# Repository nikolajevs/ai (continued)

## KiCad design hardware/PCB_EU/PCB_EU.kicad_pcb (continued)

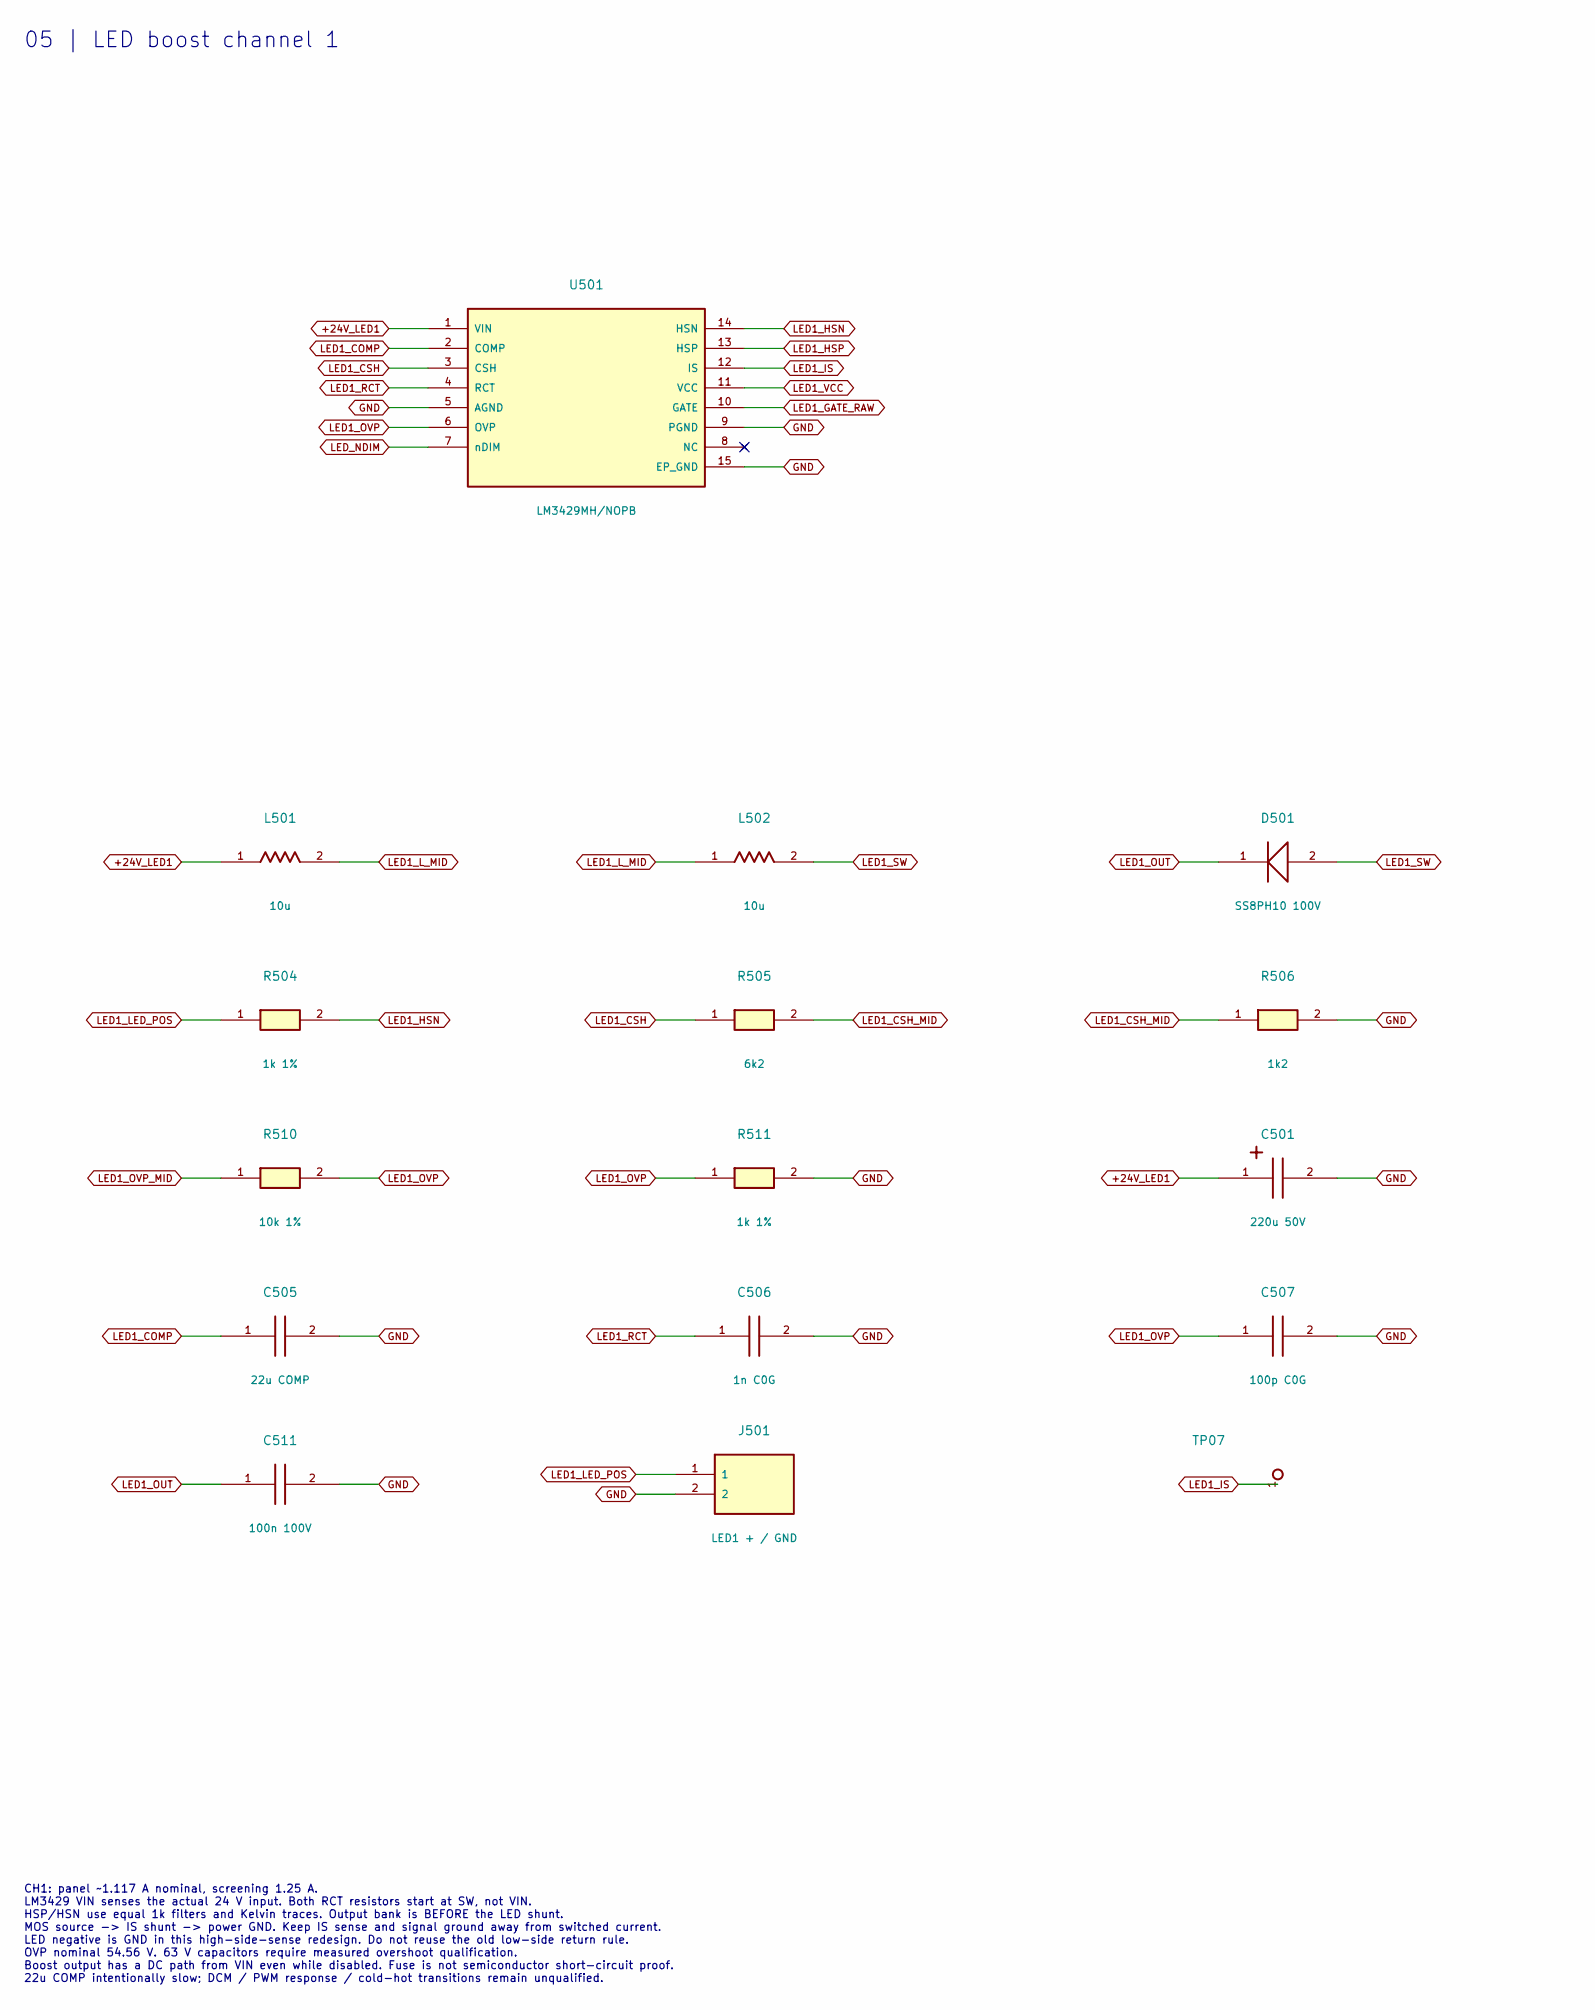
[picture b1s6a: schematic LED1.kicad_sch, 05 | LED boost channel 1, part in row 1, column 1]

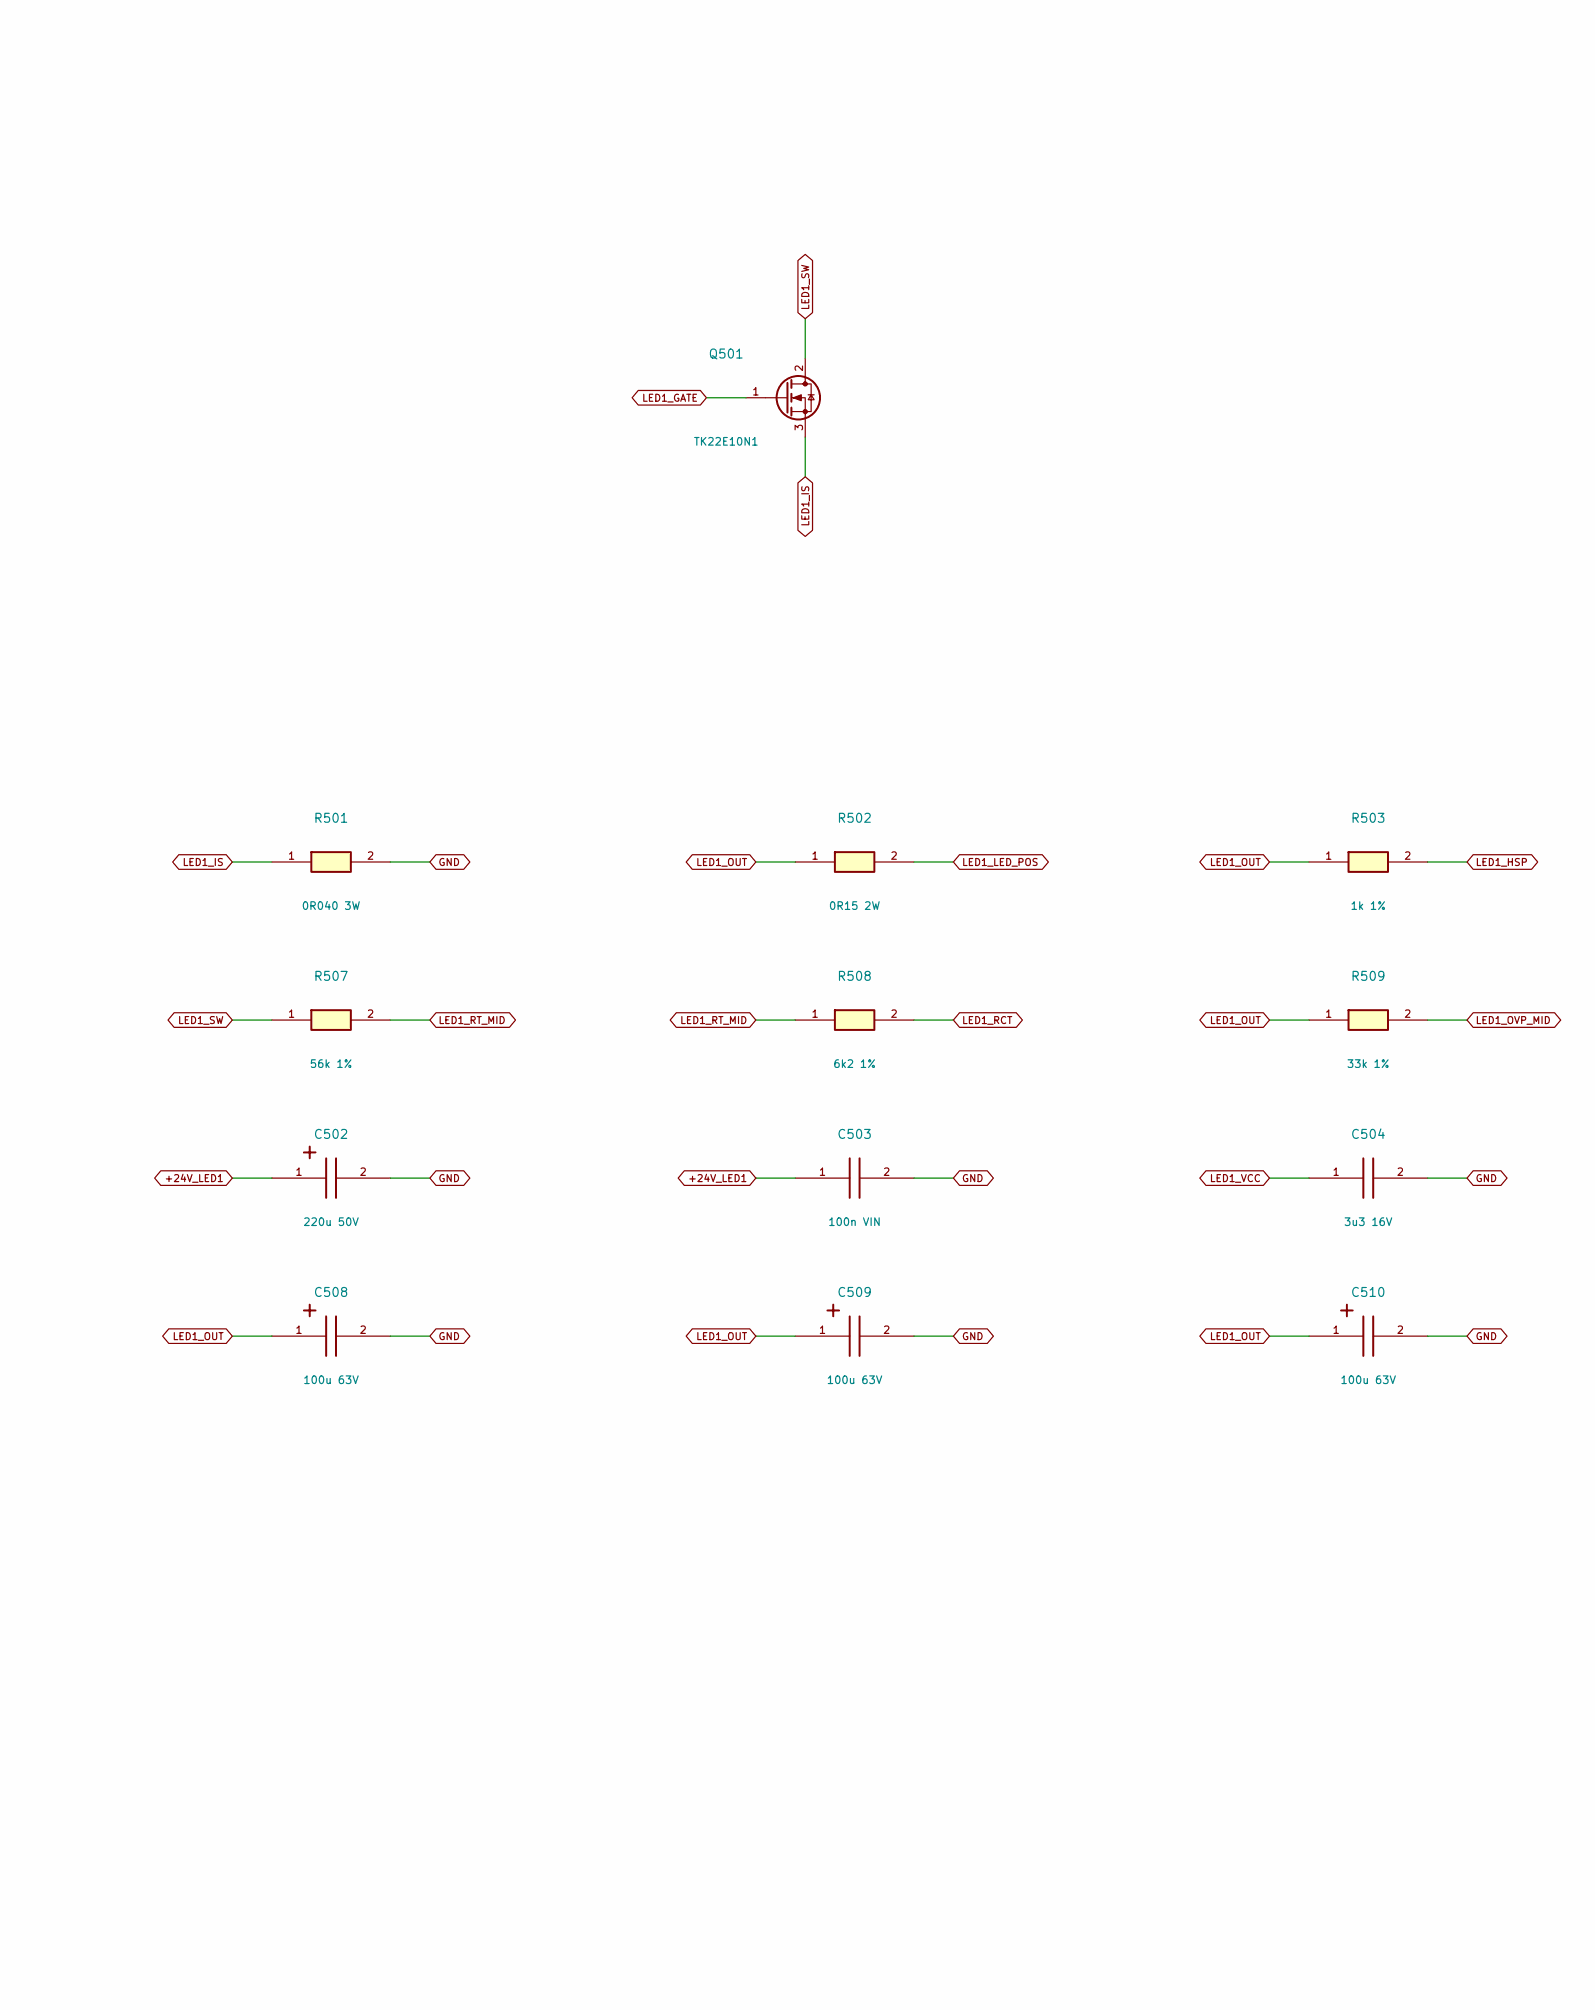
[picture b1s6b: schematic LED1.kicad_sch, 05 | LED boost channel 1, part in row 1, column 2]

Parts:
C501, C502: 220u 50V; CP_Radial_D10.0mm_P5.00mm; MPN UPW1H221MPD
C503: 100n VIN; C_0805_2012Metric; MPN CL21B104KBCNNNC
C504: 3u3 16V; C_1206_3216Metric; MPN CL31B335KOHNNNE
C505: 22u COMP; C_1206_3216Metric; MPN CL31A226KQHNNNE
C506: 1n C0G; C_1206_3216Metric; MPN C1206C102JCGACTU
C507: 100p C0G; C_1206_3216Metric; MPN CL31C101JBCNNNC
C508, C509, C510: 100u 63V; CP_Radial_D8.0mm_P5.00mm; MPN EEUFR1J101LB
C511: 100n 100V; C_0805_2012Metric; MPN C0805C104K1RACTU
D501: SS8PH10 100V; Vishay_TO-277A_D_K1_A2; MPN SS8PH10-M3/86A
J501: LED1 + / GND; TerminalBlock_Degson_DG306-5.0_1x02; MPN DG306-5.0-2P12
L501, L502: 10u; L_Jantek_JNRH1207; MPN JNRH1207-100N-A
Q501: TK22E10N1; TO-220-3_Vertical; MPN TK22E10N1
R501: 0R040 3W; R_2512_6332Metric; MPN LRP2512-R040-1%
R502: 0R15 2W; R_2512_6332Metric; MPN CS2512-0R15-1%-HP
R503, R504, R511: 1k 1%; R_1206_3216Metric; MPN SMD1206-1K-1%
R505: 6k2; R_1206_3216Metric; MPN SMD1206-6K2-1%
R506: 1k2; R_1206_3216Metric; MPN CRCW12061K20FKTABC
R507: 56k 1%; R_1206_3216Metric; MPN SMD1206 56K 1%
R508: 6k2 1%; R_1206_3216Metric; MPN SMD1206-6K2-1%
R509: 33k 1%; R_1206_3216Metric; MPN SMD1206-33K-1%
R510: 10k 1%; R_1206_3216Metric; MPN SMD1206-10K-1%
TP07: LED1_IS; TestPoint_Pad_D1.0mm
U501: LM3429MH/NOPB; TI_PWP0014A_LM3429; MPN LM3429MH/NOPB

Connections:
+24V_LED1: C501.1, C502.1, C503.1, L501.1, U501.1 (VIN); also elsewhere on the board
GND: C501.2, C502.2, C503.2, C504.2, C505.2, C506.2, C507.2, C508.2, C509.2, C510.2, C511.2, J501.2, R501.2, R506.2, R511.2, U501.5 (AGND), U501.9 (PGND), U501.15 (EP_GND); also elsewhere on the board
LED1_COMP: C505.1, U501.2 (COMP)
LED1_CSH: R505.1, U501.3 (CSH)
LED1_CSH_MID: R505.2, R506.1
LED1_GATE: Q501.1 (G); also elsewhere on the board
LED1_GATE_RAW: U501.10 (GATE); also elsewhere on the board
LED1_HSN: R504.2, U501.14 (HSN)
LED1_HSP: R503.2, U501.13 (HSP)
LED1_IS: Q501.3 (S), R501.1, TP07.1, U501.12 (IS)
LED1_LED_POS: J501.1, R502.2, R504.1
LED1_L_MID: L501.2, L502.1
LED1_OUT: C508.1, C509.1, C510.1, C511.1, D501.1 (K), R502.1, R503.1, R509.1
LED1_OVP: C507.1, R510.2, R511.1, U501.6 (OVP)
LED1_OVP_MID: R509.2, R510.1
LED1_RCT: C506.1, R508.2, U501.4 (RCT)
LED1_RT_MID: R507.2, R508.1
LED1_SW: D501.2 (A), L502.2, Q501.2 (D), R507.1
LED1_VCC: C504.1, U501.11 (VCC)
LED_NDIM: U501.7 (nDIM); also elsewhere on the board

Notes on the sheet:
05 | LED boost channel 1
CH1: panel ~1.117 A nominal, screening 1.25 A. LM3429 VIN senses the actual 24 V input. Both RCT resistors start at SW, not VIN. HSP/HSN use equal 1k filters and Kelvin traces. Output bank is BEFORE the LED shunt. MOS source -> IS shunt -> power GND. Keep IS sense and signal ground away from switch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

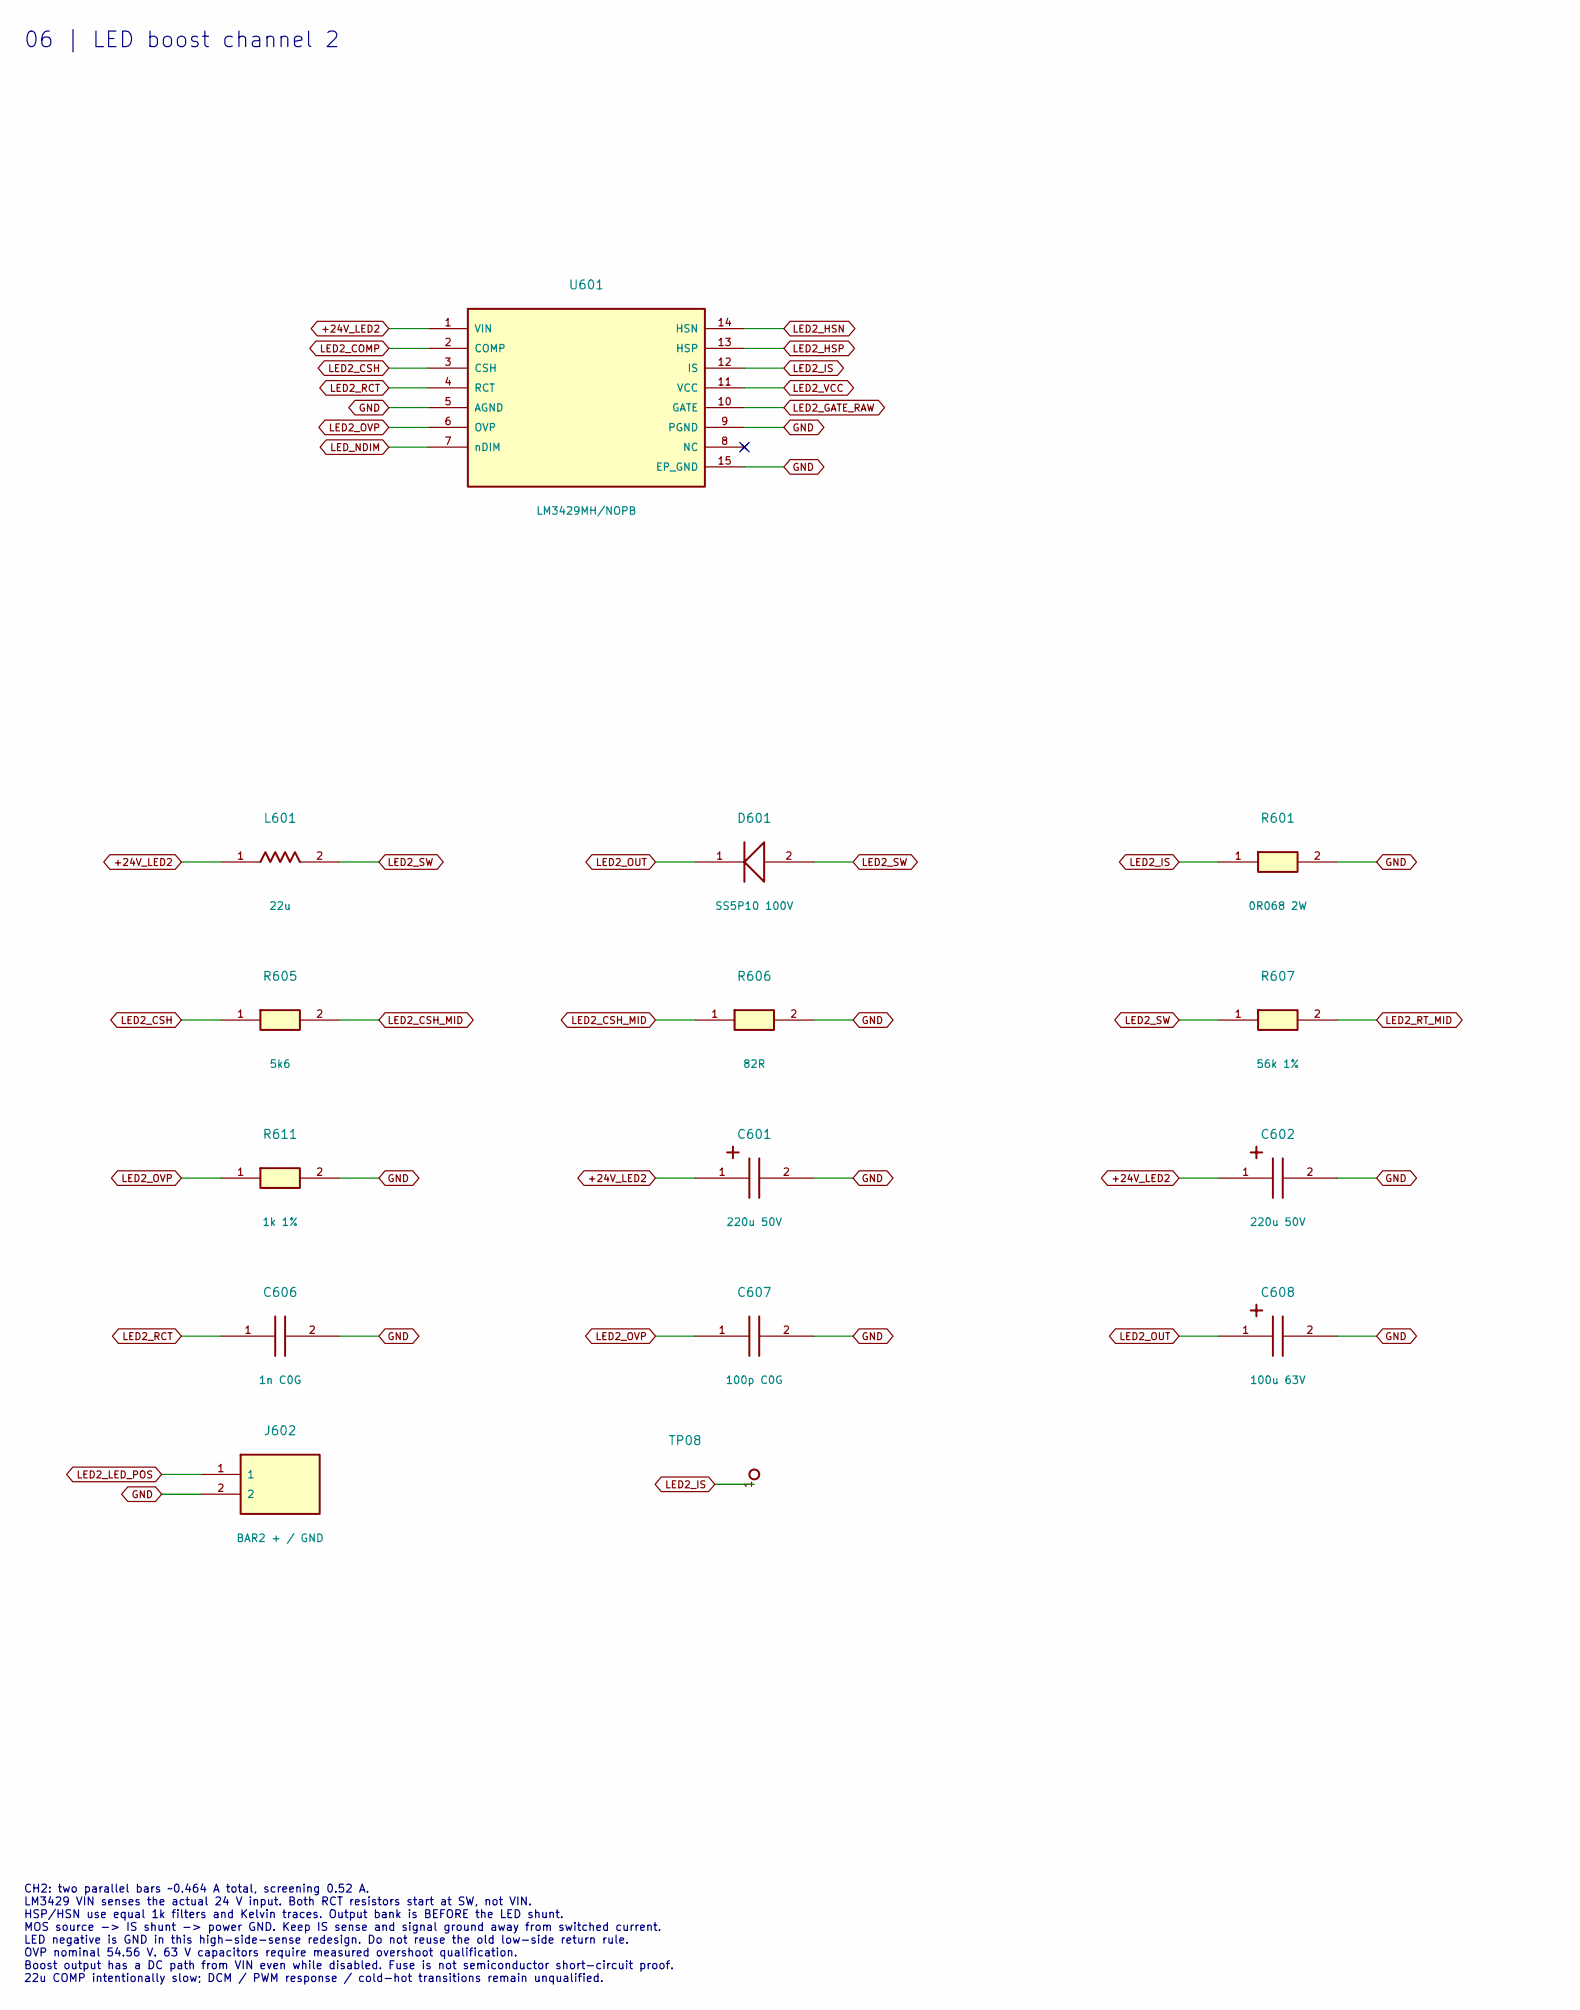
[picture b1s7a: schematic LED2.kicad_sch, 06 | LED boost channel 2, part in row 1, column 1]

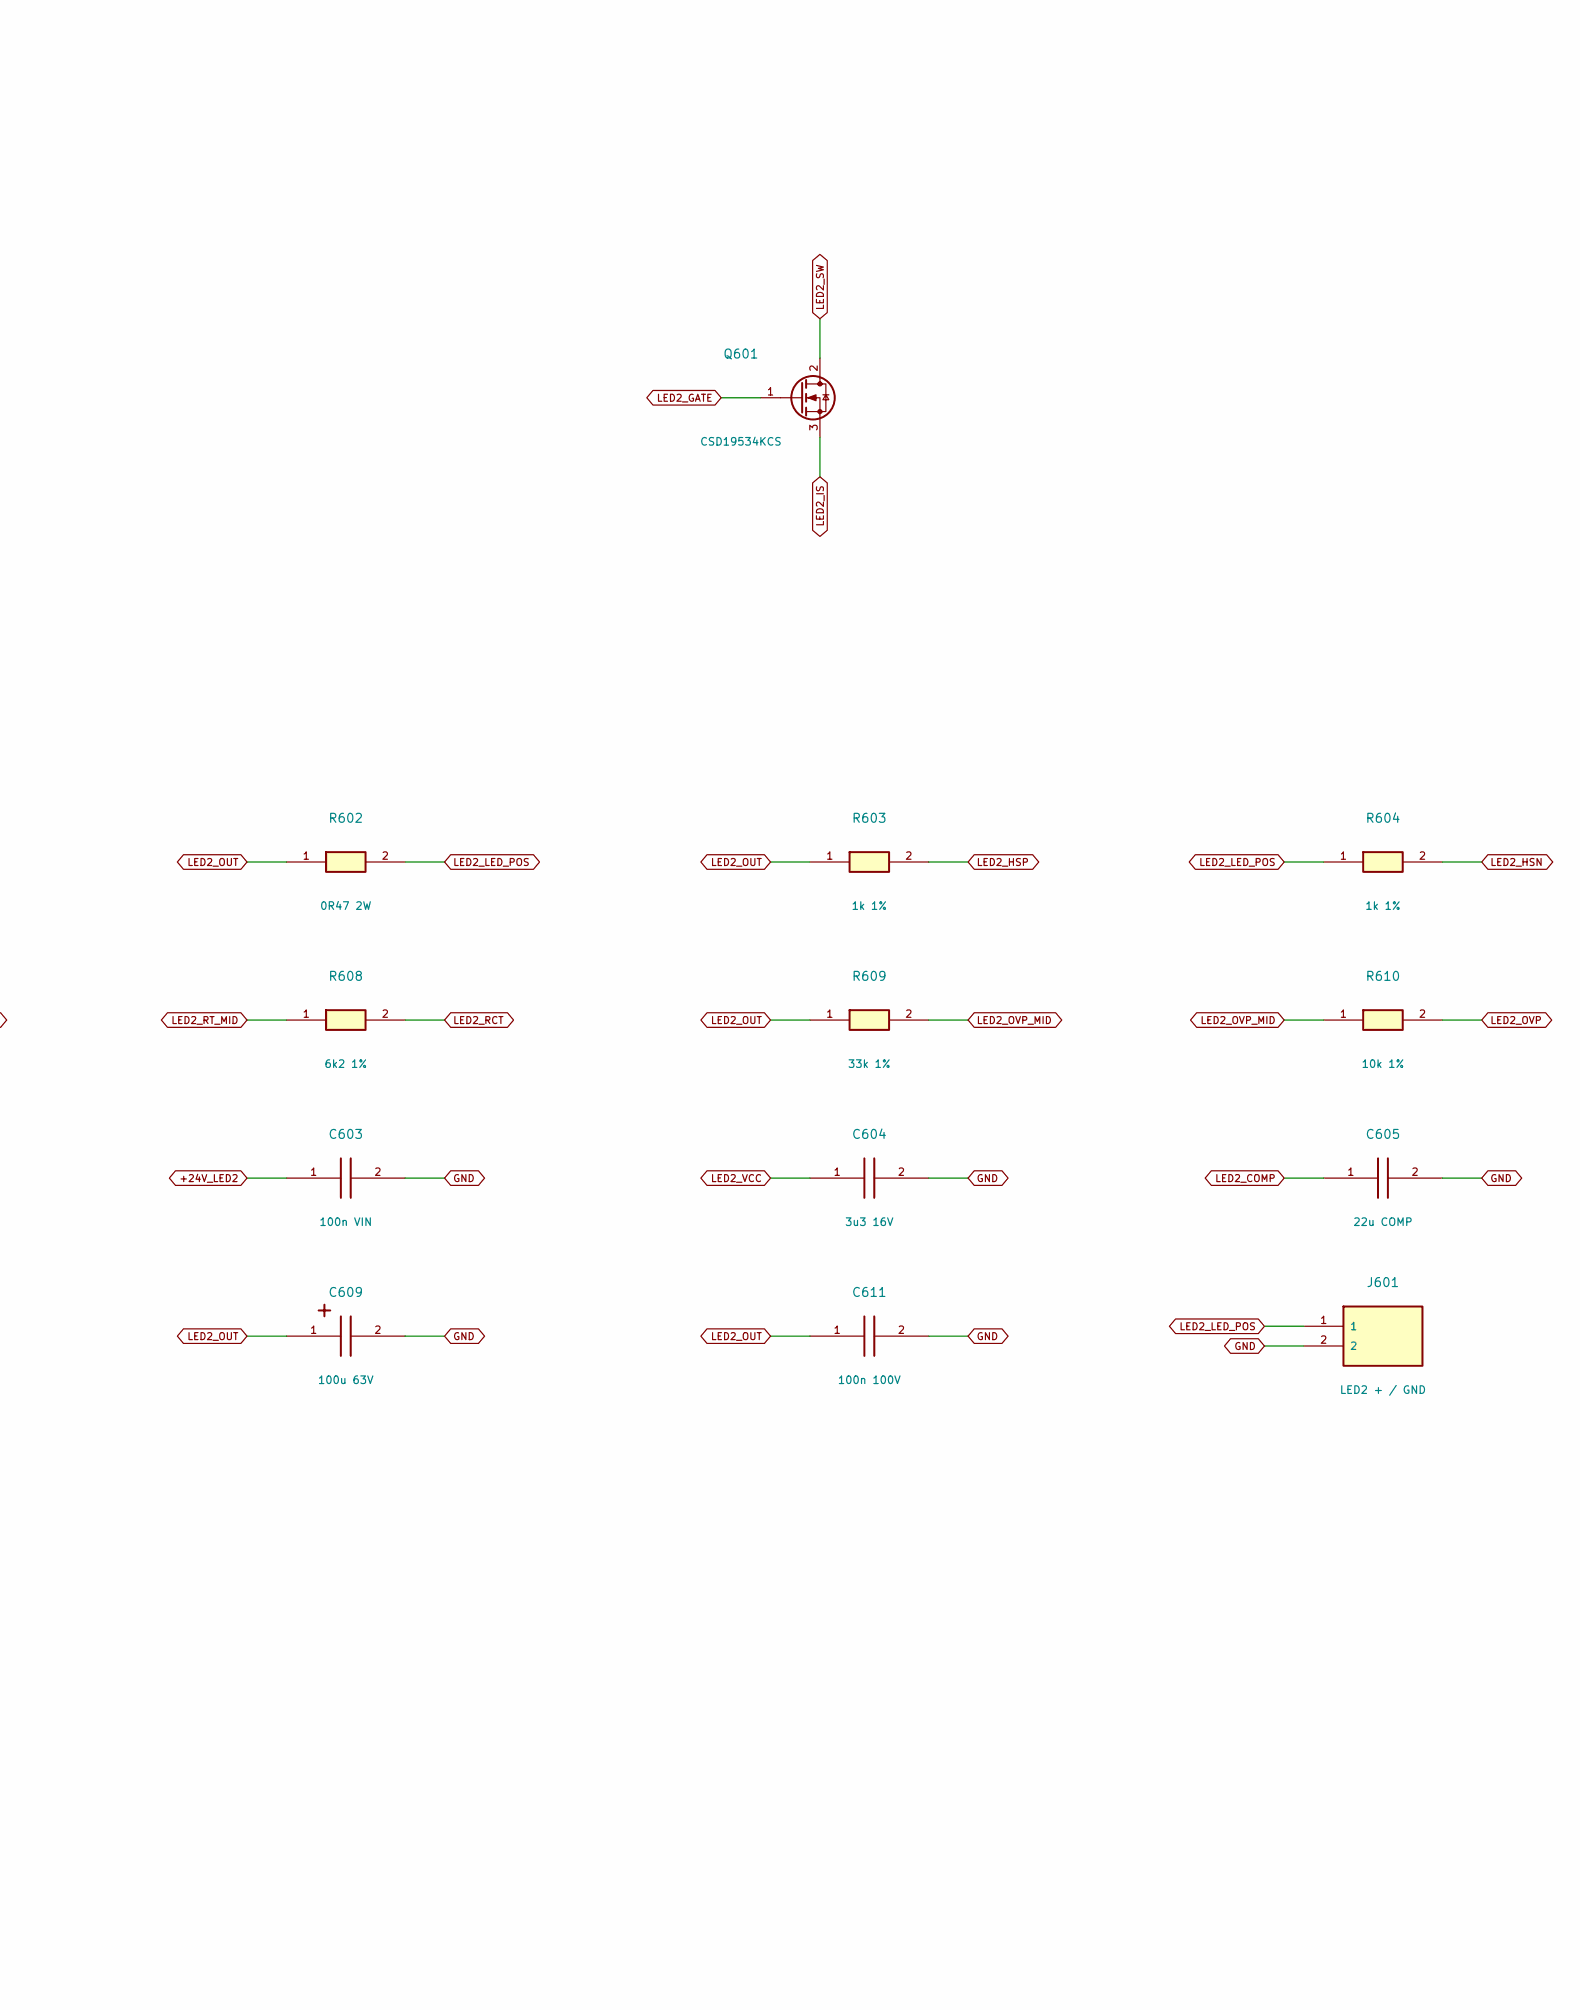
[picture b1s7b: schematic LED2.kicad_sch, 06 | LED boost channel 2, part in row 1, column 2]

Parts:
C601, C602: 220u 50V; CP_Radial_D10.0mm_P5.00mm; MPN UPW1H221MPD
C603: 100n VIN; C_0805_2012Metric; MPN CL21B104KBCNNNC
C604: 3u3 16V; C_1206_3216Metric; MPN CL31B335KOHNNNE
C605: 22u COMP; C_1206_3216Metric; MPN CL31A226KQHNNNE
C606: 1n C0G; C_1206_3216Metric; MPN C1206C102JCGACTU
C607: 100p C0G; C_1206_3216Metric; MPN CL31C101JBCNNNC
C608, C609: 100u 63V; CP_Radial_D8.0mm_P5.00mm; MPN EEUFR1J101LB
C611: 100n 100V; C_0805_2012Metric; MPN C0805C104K1RACTU
D601: SS5P10 100V; Vishay_TO-277A_D_K1_A2; MPN SS5P10-M3/86A
J601: LED2 + / GND; TerminalBlock_Degson_DG306-5.0_1x02; MPN DG306-5.0-2P12
J602: BAR2 + / GND; TerminalBlock_Degson_DG306-5.0_1x02; MPN DG306-5.0-2P12
L601: 22u; L_Jantek_JNRH1207; MPN JNRH1207-220M-A
Q601: CSD19534KCS; TO-220-3_Vertical; MPN CSD19534KCS
R601: 0R068 2W; R_2512_6332Metric; MPN CS2512-0R068-1%-HP
R602: 0R47 2W; R_2512_6332Metric; MPN CS2512-0R47-1%-HP
R603, R604, R611: 1k 1%; R_1206_3216Metric; MPN SMD1206-1K-1%
R605: 5k6; R_1206_3216Metric; MPN SMD1206 5K6 1%
R606: 82R; R_1206_3216Metric; MPN SMD1206-82R
R607: 56k 1%; R_1206_3216Metric; MPN SMD1206 56K 1%
R608: 6k2 1%; R_1206_3216Metric; MPN SMD1206-6K2-1%
R609: 33k 1%; R_1206_3216Metric; MPN SMD1206-33K-1%
R610: 10k 1%; R_1206_3216Metric; MPN SMD1206-10K-1%
TP08: LED2_IS; TestPoint_Pad_D1.0mm
U601: LM3429MH/NOPB; TI_PWP0014A_LM3429; MPN LM3429MH/NOPB

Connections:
+24V_LED2: C601.1, C602.1, C603.1, L601.1, U601.1 (VIN); also elsewhere on the board
GND: C601.2, C602.2, C603.2, C604.2, C605.2, C606.2, C607.2, C608.2, C609.2, C611.2, J601.2, J602.2, R601.2, R606.2, R611.2, U601.5 (AGND), U601.9 (PGND), U601.15 (EP_GND); also elsewhere on the board
LED2_COMP: C605.1, U601.2 (COMP)
LED2_CSH: R605.1, U601.3 (CSH)
LED2_CSH_MID: R605.2, R606.1
LED2_GATE: Q601.1 (G); also elsewhere on the board
LED2_GATE_RAW: U601.10 (GATE); also elsewhere on the board
LED2_HSN: R604.2, U601.14 (HSN)
LED2_HSP: R603.2, U601.13 (HSP)
LED2_IS: Q601.3 (S), R601.1, TP08.1, U601.12 (IS)
LED2_LED_POS: J601.1, J602.1, R602.2, R604.1
LED2_OUT: C608.1, C609.1, C611.1, D601.1 (K), R602.1, R603.1, R609.1
LED2_OVP: C607.1, R610.2, R611.1, U601.6 (OVP)
LED2_OVP_MID: R609.2, R610.1
LED2_RCT: C606.1, R608.2, U601.4 (RCT)
LED2_RT_MID: R607.2, R608.1
LED2_SW: D601.2 (A), L601.2, Q601.2 (D), R607.1
LED2_VCC: C604.1, U601.11 (VCC)
LED_NDIM: U601.7 (nDIM); also elsewhere on the board

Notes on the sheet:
06 | LED boost channel 2
CH2: two parallel bars ~0.464 A total, screening 0.52 A. LM3429 VIN senses the actual 24 V input. Both RCT resistors start at SW, not VIN. HSP/HSN use equal 1k filters and Kelvin traces. Output bank is BEFORE the LED shunt. MOS source -> IS shunt -> power GND. Keep IS sense and signal ground away f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
